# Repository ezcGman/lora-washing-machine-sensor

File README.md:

# LoRA Washing Machine & Dryer Sensor
A small ESP8266 & RFM95W based sensor board that utilizes CT clamps to measuer your washing machine and dryers power consumption and report the reading via LoRa, e.g. to my [LoRa-To-MQTT-Gateway](https://github.com/ezcGman/lora-gateway)! Using LoRa enables you to also get reading froma washing machine hidden in the far end of a basement and report the readings multiple floors up to your apartment that hosts the LoRa gateway (and probably your Home Assistant).

---

**WARNING: This project will require you do mains / AC wiring! If you have never done that and don't know what you're doing: Don't read further!**

---

## Credits
As for all my PCBs: Huge thanks to Quindor from QuinLED.info and also the folks from #pcb-design-talk on his Discord server! Would not have been able to do anything without these people!!

## KiCad dependencies
It might happen that KiCad is missing my custom footprints. You can find and download them here and then add them to KiCad: https://github.com/ezcGman/andys-footprints

## Key features
- Very small size, fits in small DIY boxes
- 5-18V support! However, I recommend powering it with 12V max; the heat that LDO will produce might be a bit much.
- External Antenna!
- The ESP sits on pin headers instead of being soldered onto it. This enables you to remove / exchange it, e.g. if your code on that ESP doesn't have any OTA update feature, or if you want to exchange it for another ESP type
- Mounting holes to screw it onto something
- Made in Germany! ;)

## What do I need to do to get one?
### 1. Get the PCBs
You want to get the PCBs printed at a PCB prototype factory of your choice, like JLCPCB or PCBWay. I've included the Gerber files for both in the respective folder. If you want to use a different service provider, you need to check if they may accept these Gerbers or generate them yourself.

### 2. Get the components
Please see the [iBOM](/ibom/ESPBreakoutBoard-Min-Cutout-v4r3.html), which you can find in the `ibom` folder: It lists most components (except the ones below) to easily find them on AliExpress, LCSC or your preferred component sourcing platform :)

#### Extra Parts
These parts are not directly listed in the iBOM or need some further detail links:
- RFM95W, the famous low-cost LoRa module: https://www.aliexpress.com/wholesale?SearchText=rfm95w
- YHDC SCT-013, the CT clamps to actually measure power: https://www.aliexpress.com/wholesale?SearchText=sct-013
    - Get the 10A one, 15A at the maximum; you don't need more. I personally use the 15A ones in my install and code, just because I had them.
- The socket / jack for the external antenna: This can get a bit tricky and you may need to search AliExpress a tiny bit. The key important facts are a bit hard to state, as every seller lists something different:
    - The actual spacing of the outer holes from middle to middle of the hole is 5.08mm
    - Some sellers list the outer spacing of the pins, which is 6mm
    - Some just list the inner spacing of the pins, which is 4mm
    - But all of the above are ok, they gonna fit. There's also a [picture here](/pictures/rf-jack-spacing.jpg) to maybe help clarifying things
    - This seller always has a bunch at the time of writing: https://www.aliexpress.com/store/1100046103

### 3. Build the board and choose a power supply
Again, check the iBOM HTML file which gives you nice soldering instructions / overview, find it in the `ibom` folder. When you've soldered the board, wire it up with a 5V power source: It consumes less than 300mA, so you can easily use an old 500mA, 1A (or higher) phone charger for it.

### 4. Find the correct calibration value for the CT clamp
Or just trust me :)

Seriously: The library that actually reads current measurement values from the CT clamps needs a "calibration" value. This can vary on quite a few factors, but you can *roughly* say: If you have a 15A clamp, the value is somewhat near that number. For me, 14 gave the most accurate readings. Ultimately for this sensor, we don't really care about accurate readings, just readings / knowing if the machine still runs or is finished.

If you actually want to get an accurate calibration value, Edis Tech Lab (sorry, German!) [made a great video](https://www.youtube.com/watch?v=zNbtCse6n3s) about the CT clamps themselves and also talks a bit about how to find the correct calibration value.

### 5. Install the software
This board is designed to work with my [LoRa-To-MQTT-Gateway](https://github.com/ezcGman/lora-gateway), hence the source is also designed around it. Feel free to develop your own code, if yout want!

Source is available in the `src` folder. Download Arduino IDE and check a few things before you compile:
1. Near the top of `lora-washing-machine-sensor.ino`, change the calibration value [according to 4. above](#4-find-the-correct-calibration-value-for-the-ct-clamp): `const byte ctClampCalibration = 14;`
2. Download `lora-ids.h` and `utils.h` from the [LoRa-To-MQTT-Gateway repo](https://github.com/ezcGman/lora-gateway/tree/master/src/lora-gateway-e32) and place them into the source code folder, effectively replacing the placeholders there.
3. If you gave your LoRa-Gateway a different ID than `0x1`, change it in `lora-config.h`: `#define LORA_GATEWAY_ID 0x1 // 1`
4. That's it: Compile and upload it to your ESP8266 module

### 6. Hook up your washing machine
Now it gets a bit tricky and again: If you have never done AC / mains wiring and especially if you're in an apartment building / rented home: Leave your fingers off the AC wiring: If you don't know what you're doing and if you're not careful, you may up hurting yourself or others with your install!

OK, so now that we got that sorted out: CT clamps can't just go around your 3-core power cable of your washing machine: They can only measure current if you install them around either the L or N wire, not both, only a single one. So you need to get creative on how you get access to that wire.

What I did (you can [see some photos here](/pictures/install-pics)) is getting three AC power sockets and mounted them to a box. Why three?
- One as power in, coming from the wall
- One to plug in the washing machine
- One to plug in the dryer

With this, I do not touch the actual cables of the machines, plus: I do not have loose wires around! Inside the box, the two sockets (where the washing machine and dryer will be plugged into) are simply powered by the socket the power comes in, BUT: By using some Wagos, I can easily put the CT clamp around the L wire of the socket the machine and dryer is connected to.

Additionally, I modified a standard / cheap 1A phone charger by sawing off the two pins that would go into a power socket and instead soldered two wires to the PCB that then go into the Wagos inside the Box. And the 5V USB output goes to the PCB :) Pics are also in the same folder as above.

With this, you have a safe and clean install, no AC wires open and you can easily put that box behind the machine and dryer.

### 7. Read the values in Home Assistant
This is pretty easy:

First create two MQTT sensors that will read the watts from the MQTT topic the gateway will drop the readings into:
```
mqtt:
  sensor:
  - name: "[Basement] Washing Machine Watts"
    state_topic: "lora-gateway-e32/devices/washing-machine-sensor/messages/power-consumption/watts"
    icon: mdi:flash

  - name: "[Basement] Dryer Watts"
    state_topic: "lora-gateway-e32/devices/dryer-sensor/messages/power-consumption/watts"
    icon: mdi:flash
```

Now we create two `input_boolean` helpers that will make writing the automations easier. They will simply store the "result" of an automation that detects if a machine is running:
```
washing_machine_status:
  name: "[zzz-Helpers] Washing Machine Status"
  initial: off
  icon: mdi:washing-machine
  
dryer_status:
  name: "[zzz-Helpers] Dryer Status"
  initial: off
  icon: mdi:tumble-dryer
```

And now, we can create two automations per machine to first check if it started and another one that detects if it's finished. You may wanna do a few runs of your machine to get some test data and see what can really be considered "finished". Our machine sometimes does a tiny break and doesn't consume anything. So I declare the machine being finished if the readings show a value below 15W for at least two minutes, to not fall for those tiny breaks:
```
- id: washing_machine_started_set_helper
  alias: "[zzz-Helpers] Set helper sensor if washing machine is running"
  trigger:
  - platform: numeric_state
    entity_id: sensor.basement_washing_machine_watts
    above: 1000
  condition:
  - condition: state
    entity_id: input_boolean.washing_machine_status
    state: 'off'
  action:
  - service: input_boolean.turn_on
    data:
      entity_id: input_boolean.washing_machine_status
      
- id: washing_machine_finished
  alias: "[Basement] Send notification and reset helper if washing machine has finished"
  trigger:
  - platform: numeric_state
    entity_id: sensor.basement_washing_machine_watts
    below: 15
    for: 00:02:00
  condition:
  - condition: state
    entity_id: input_boolean.washing_machine_status
    state: 'on'
  action:
  - service: input_boolean.turn_off
    data:
      entity_id: input_boolean.washing_machine_status
  - service: notify.all_phones
    data:
      title: "🧺 Washing Machine finished!"
      message: "Get that laundry out there quickly!"
```

## Tools list to solder the PCB
### Required
- A soldering iron
- Soldering tin

### Optional
- For SMD components:
  - A hot air soldering/reflow station. However, it's only two and u have space around them, so they can be done with a soldering iron. Also the LDO can be technically soldered with an iron.
  - Solder paste
  - Tweezers

## FAQ
### Why the AMS117? Why not another LDO?
Because: I have so many lying around here ¯\\_(ツ)\_/¯ It's not the best, but pretty famous, cheap and easy to get LDO. It theoretically can eat up to 18V, so you could power that board with 18V, if you wanted to. Not talking about the heat this thing generates, if you would ;)

Its downsides are clearly the quiescent current of at least 5mA up to 13mA! There are also smaller LDOs (the AMS1117 is SOT-223), but with that screw terminal I wanted, it wouldn't matter anyways.
If you want to change it, you're welcome to edit the PCB using KiCad :)

### You're routing the SPI traces under the ESP antenna!
Yes, I do :) And I know that it's usually a no-go to route (high speed) data traces under an RF antenna. But in this case, that's fine, because we're not using Wi-Fi: My source code turns off the antenna completely, waits for it to be actually off and then starts initializing the LoRa module using SPI.

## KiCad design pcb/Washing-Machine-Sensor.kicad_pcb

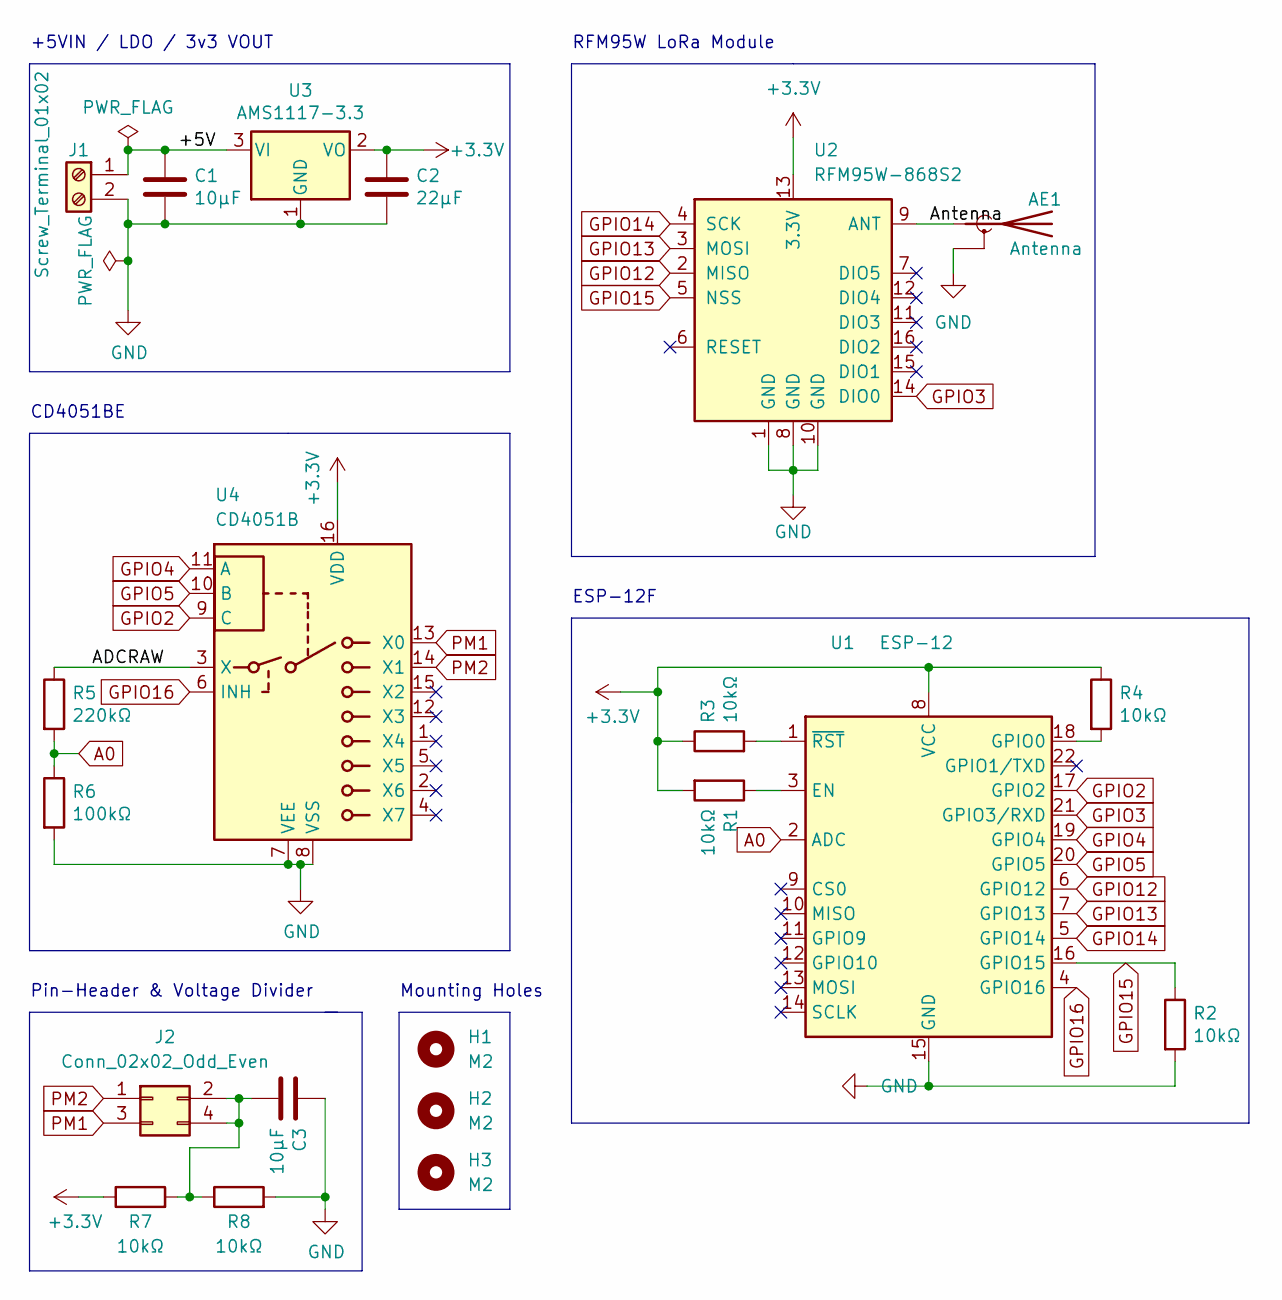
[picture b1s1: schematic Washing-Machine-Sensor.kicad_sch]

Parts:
AE1: Antenna; SMA_Molex_73251-2200_Horizontal
C1, C3: 10µF; C_0805_2012Metric
C2: 22µF; C_0805_2012Metric
H1, H2, H3: M2; MountingHole_2.2mm_M2_Pad_Via
J1: Screw_Terminal_01x02; TerminalBlock_Phoenix_MPT-0,5-2-2.54_1x02_P2.54mm_Horizonta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
J2: Conn_02x02_Odd_Even; PinHeader_2x02_P2.54mm_Horizontal
R1, R2, R3, R4, R7, R8: 10kΩ; R_0805_2012Metric
R5: 220kΩ; R_0805_2012Metric
R6: 100kΩ; R_0805_2012Metric
U1: ESP-12; ESP-12-Socket
U2: RFM95W-868S2; HOPERF_RFM9XW_THT_Fixed_Size
U3: AMS1117-3.3; SOT-223-3_TabPin2
U4: CD4051B; DIP-16_W7.62mm

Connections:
+3V3: C2.1, R1.2, R3.1, R4.1, R7.1, U1.8 (VCC), U2.13 (3.3V), U3.2 (VO), U4.16 (VDD)
/+5V: C1.1, J1.1, U3.3 (VI)
/ADCRAW: R5.1, U4.3 (X)
/Antenna: AE1.1 (A), U2.9 (ANT)
A0: R5.2, R6.1, U1.2 (ADC)
GND: AE1.2 (Shield), C1.2, C2.2, C3.1, J1.2, R2.2, R6.2, R8.2, U1.15 (GND), U2.1 (GND), U2.8 (GND), U2.10 (GND), U3.1 (GND), U4.7 (VEE), U4.8 (VSS)
GPIO2: U1.17 (GPIO2), U4.9 (C)
GPIO3: U1.21 (GPIO3/RXD), U2.14 (DIO0)
GPIO4: U1.19 (GPIO4), U4.11 (A)
GPIO5: U1.20 (GPIO5), U4.10 (B)
GPIO12: U1.6 (GPIO12), U2.2 (MISO)
GPIO13: U1.7 (GPIO13), U2.3 (MOSI)
GPIO14: U1.5 (GPIO14), U2.4 (SCK)
GPIO15: R2.1, U1.16 (GPIO15), U2.5 (NSS)
GPIO16: U1.4 (GPIO16), U4.6 (INH)
unnamed: C3.2, J2.2, J2.4, R7.2, R8.1
unnamed: R1.1, U1.3 (EN)
unnamed: R3.2, U1.1 (~RST)
unnamed: R4.2, U1.18 (GPIO0)
PM1: J2.3, U4.13 (X0)
PM2: J2.1, U4.14 (X1)

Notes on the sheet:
CD4051BE
Pin-Header & Voltage Divider
RFM95W LoRa Module
Mounting Holes
+5VIN / LDO / 3v3 VOUT
ESP-12F

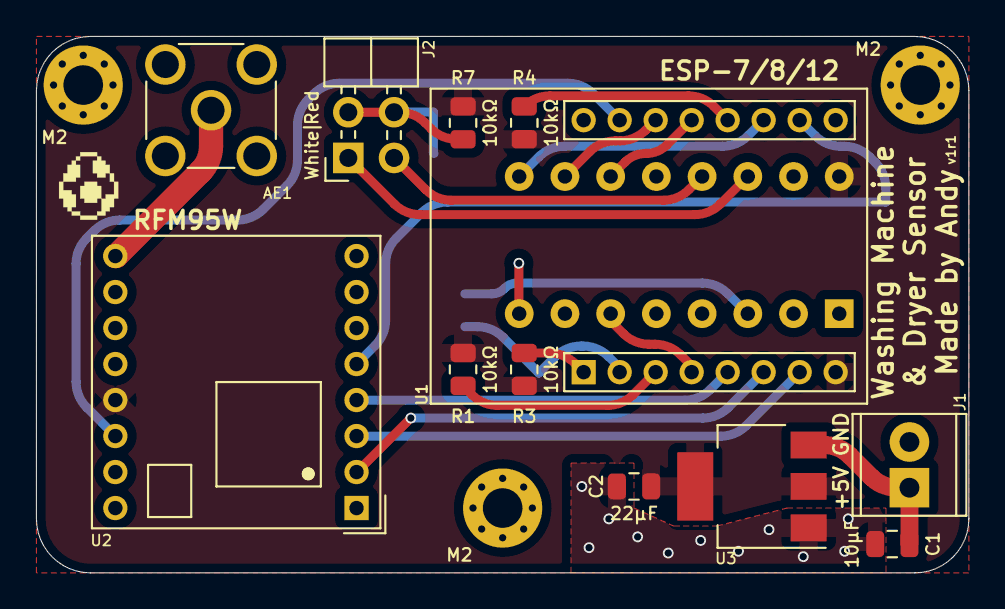
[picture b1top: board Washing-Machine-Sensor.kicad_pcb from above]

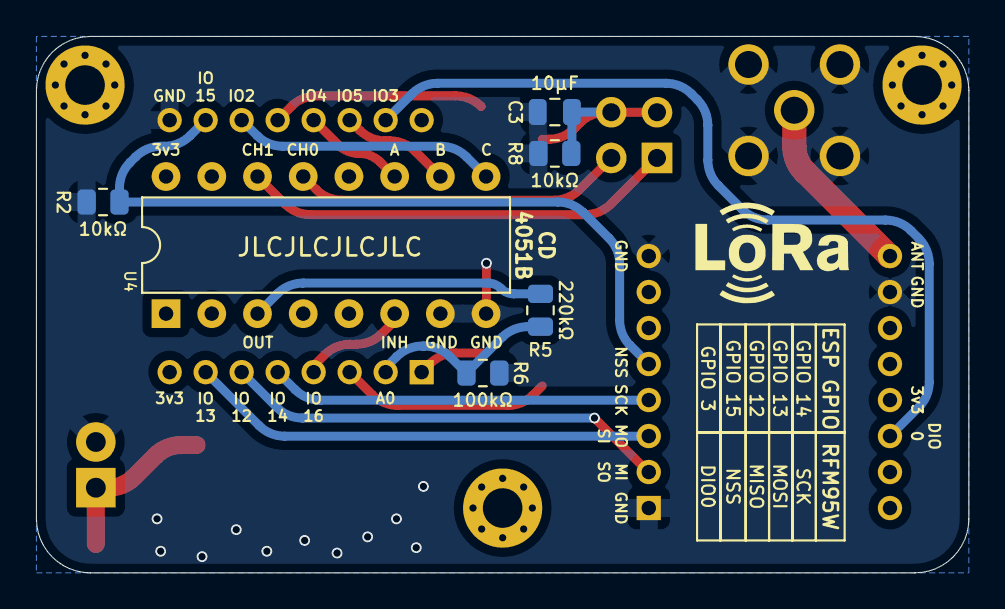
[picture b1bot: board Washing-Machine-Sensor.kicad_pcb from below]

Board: 2 copper layers, 51.8 x 29.8 mm, 23 parts (7 on the bottom side), 21 nets.

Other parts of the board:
G1: LOGO; Yoshi-Egg-Small
G2: LOGO

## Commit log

2022-09-27 First commit of v1r1
2022-09-27 Remove unneccessary PCB backup files
2022-09-28 Added source code
2022-09-28 Using new sendLoRaMessage function
2022-09-29 Completed Readme, added iBOM
2022-09-29 Added RF jack pic
2022-10-04 Added install pics
